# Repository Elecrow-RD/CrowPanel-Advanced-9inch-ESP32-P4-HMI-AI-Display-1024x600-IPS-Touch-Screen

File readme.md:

### 1, Product picture

### 2, Product version number

|      | Hardware | Software | Remark |
| ---- | -------- | -------- | ------ |
| 1    | V1.0     | V1.0     | old |
| 1    | V1.1     | V1.1     | old |
| 1    | V1.2     | V1.2     | latest |

**Version 1.1 Update**

The C6 module version 1.1 adds support for 4-wire SDIO communication. Additionally, the arrangement of the SDIO pins has been adjusted, with the pin mappings of the data lines D0–D3 changing from **IO14, IO15, IO16, IO17** to **IO17, IO16, IO15, IO14**. 

**Version 1.2 Update** 

Based on the V1.1 version, V1.2 further optimized the communication stability of the LoRa wireless module. At the same time, the signal pins of the wireless module socket were re-allocated: the original **IO53 and IO54** were adjusted to **IO27 and IO28** respectively, and correspondingly, **IO27 and IO28** were adjusted to **IO53 and IO54** respectively.

### 3, product information

| **Main Chip-ESP32-P4NRW32**                  |                                                              |
| -------------------------------------------- | ------------------------------------------------------------ |
| CPU/SoC                                      | **ESP32-P4**RISC-V 32-bit dual-core processor for HP systems, running at up to 400 MHz; RISC-V 32-bit single-core processor for LP systems, running at up to 40 MHz |
| System Memory                                | 768 KB L2MEM（HP）32 KB SRAM（LP）8 KB TCM 32 MB PSRAM       |
| Memory                                       | 128 KB ROM（HP）16 KB ROM（LP）16 MB Flash                   |
| Development Environment                      | ESP-IDF、Arduino IDE                                         |
| **Screen**                                   |                                                              |
| Size                                         | 9.0 inch                                                     |
| Resolution                                   | 1024*600                                                     |
| Display Panel                                | IPS Panel                                                    |
| Touch Panel                                  | Capacitive Touch, Single/5-point Touch                       |
| Viewing Angle                                | 178°                                                         |
| Brightness                                   | 400 cd/m²(Typ.)                                              |
| Color Depth                                  | 16.7M (8-bit)                                                |
| **Wireless Communication - Onboard Antenna** |                                                              |
| WiFi                                         | Support 2.4GHz(Wi-Fi6), 802.11a/b/g/n                        |
| Bluetooth                                    | Support Bluetooth 5.3 and BLE                                |
| Other                                        | Zigbee、LoRa、nRF2401、Matter、Thread and Wi-Fi Halow (Optional) |
| **Interface/Function**                       |                                                              |
| Interface                                    | USB2.0, UART, I2C, GPIO female headers, SD card holder, battery socket, speaker jack, camera header, module female headers, etc. |
| Function                                     | Audio amplifier, battery charge management, USB to UART, dual microphones, etc. |
| **Button/LED Indicator**                     |                                                              |
| Reset Button                                 | Yes, press to reset device                                   |
| Boot Button                                  | Yes, press and hold the power button to burn the program     |
| Power Button                                 | Switch On/Off                                                |
| PWR                                          | Device power on/off indication                               |
| CHG                                          | Lithium battery charging status, Low battery state           |
| **Other**                                    |                                                              |
| Installation method                          | All around mounting holes(M3 3.2mm), embedded, shell assembly |
| Operating temperature                        | -20~70 °C                                                    |
| Storage temperature                          | -30~80 °C                                                    |
| Power Input                                  | 5V/2A, USB or UART terminal                                  |
| Dimensions                                   | 222\*130*16mm                                                |

### Functional description of the product's internal interfaces:

| Pin Name | Description                                                  | Connector Type |
| :------- | :----------------------------------------------------------- | :------------- |
| SPK      | Output audio signals to connect to speakers. The main board comes with a power amplifier chip circuit. | PH2.0-2P       |
| PWR      | Power LED.                                                   |                |
| RST      | Reset button. Press it to reset the system.                  |                |
| boot     |                                                              |                |
| UART1    | Builds communication between Logic modules, including the serial communication module and the print module. | HY2.0-4P       |
| I2C      | Builds communication between Logic modules, including the serial communication module and the print module. | HY2.0-4P       |
| UART3-IN | Input power supply and serial communication functionality    | XH2.54-4P      |
| BAT      | Connect the lithium battery. (with battery charging circuit) | PH2.0-2P       |

### 4, Use the driver module

| Name | dependency library |
| ---- | ------------------ |
| LVGL | lvgl/lvgl@9.1(V1.2)<br />lvgl/lvgl@8.3(V1.0/V1.1) |

### 5,Quick Start
##### ESP-IDF starts

**Note**: This is an IDF course. Before proceeding, ensure you have Visual Studio Code and the **IDF **environment installed. The IDF version must be **5.4.2 **or higher.

1.Right-click on an empty space in the project folder and select "Open with VS Code" to open the project.

2.In the IDF plug-in, select the port, then compile and flash

### 6,Folder structure.
|--3D file： Contains 3D model files (.stp) for the hardware. These files can be used for visualization, enclosure design, or integration into CAD software.

|--Datasheet: Includes datasheets for components used in the project, providing detailed specifications, electrical characteristics, and pin configurations.

|--Eagle_SCH&PCB: Contains **Eagle CAD** schematic (`.sch`) and PCB layout (`.brd`) files. These are used for circuit design and PCB manufacturing.

|--example: Provides example code and projects to demonstrate how to use the hardware and libraries. These examples help users get started quickly.

|--factory_firmware: Stores pre-compiled factory firmware that can be directly flashed onto the device. This ensures the device runs the default functionality.

|--factory_sourcecode:  Contains the source code for the factory firmware, allowing users to modify and rebuild the firmware as needed.

|--libraries: Includes necessary libraries required for compiling and running the project. These libraries provide drivers and additional functionalities for the hardware.

### 7,Pin definition

#### ESP32-P4 9 inch and IPS Display Wiring Pins:
**DSI = Display Serial Interface**is a high-speed, low-power display interface standard defined by the MIPI Alliance, most commonly used in smartphones, tablets, Raspberry Pi devices, and embedded Linux systems.

DSI Pin connection

DSI_DATAN0--IO40

DSI_DATAN0--IO39

DSI_DATAN0--IO36

DSI_DATAN0--IO35

DSI_CLKN--IO37

DSI_CLKP--IO38

DSI_REXT--IO34

#### ESP32-P4 and Touch Driver Wiring：

i2c address: 0x5D/0x14.(The INT pin level during reset of the GT911 touch chip determines the device address.)

INT Low Level(0x5D);

INT High Level(0x14).

Pin connection

I2C1_SCL(IO46)

I2C1_SDA(IO45)

INT_TP(IO42)

RESET_TP(IO40)

#### ESP32-P4 and wireless module wiring pins：

Output voltage: 3.3V Output current: 1A max. Use: The power supply communicates with the wireless module.

Pin connection

#define RADIO_GPIO_CLK 8

#define RADIO_GPIO_MISO 7

#define RADIO_GPIO_MOSI 6

#ifdef CONFIG_BSP_SX1262_ENABLED

#define SX1262_GPIO_BUSY 9

#define SX1262_GPIO_IRQ 53

#define SX1262_GPIO_NRST 54

#define SX1262_GPIO_NSS 10

#ifdef CONFIG_BSP_NRF2401_ENABLED

#define NRF24_GPIO_IRQ 9

#define NRF24_GPIO_CE 53

#define NRF24_GPIO_CS 54

ESP32-P4 and Audio out：

Pin connection

#define AUDIO_GPIO_LRCLK    21   // GPIO pin number for LRCLK (Left-Right Clock)

#define AUDIO_GPIO_BCLK     22   // GPIO pin number for BCLK (Bit Clock)

#define AUDIO_GPIO_SDATA    23   // GPIO pin number for SDATA (Serial Data)

#define AUDIO_GPIO_CTRL     30   // GPIO pin number for audio amplifier control

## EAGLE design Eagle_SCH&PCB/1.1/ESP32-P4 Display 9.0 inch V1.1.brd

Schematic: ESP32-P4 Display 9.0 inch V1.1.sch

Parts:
0R/2A: 0R/800mA; L0805
C1, C2, C3, C10, C17, C22, C69, C86, C102, C143: 1uF; 0603
C4: 10uF/NC; 0603
C5, C7, C9, C36, C39, C40, C41, C43, C45, C46, C50, C60, C61, C63, C72, C73, C108, C113, C115, C130, C132, C145: 100nF; C0402
C6, C8, C42, C44, C47, C48, C49, C56, C71, C107, C112, C114, C116: 10uF; C0402
C11, C15, C19, C20, C21, C35, C37, C52, C53, C54, C75, C76, C77, C80, C81, C82, C84, C135, C144, C147, C150, C151, C152, C154, C155, C156, C159, C169: 100nF; 0603
C12, C27, C28, C32: 10uF/10V+; 0603
C13, C18: 22uF; C0805
C14, C16, C38, C74, C78, C79, C83, C136, C149, C153, C157: 10uF; 0603
C23, C24, C103, C104, C134, C148: 47uF; 0603
C25, C160, C161, C162, C163, C164, C165, C166, C167, C168: 10pF_NC; C0402
C26, C31: 22pF; 0603
C29, C30: 12pF; C0402
C33, C34: 15pF; C0402
C51, C55, C57, C58, C59, C64, C65, C66, C117, C118, C119, C120, C121, C122, C123, C124, C125, C126, C127, C128, C129, C131, C133, C137, C138, C139, C140, C141, C142, C146: 1uF; C0402
C62: 10nF; C0402
C67, C68, C85, C105, C106, C158: 1nF; 0603
C70: 10UF; 0603
C87: 15pF; 0603
C88: 10UF_NC; 0603
C89, C101: 22pF; C0402
C90, C99, C110: 10uF/25V; 0603
C91, C100, C111: 100nF/50V; 0603
C92: 22uF/16V; C0805
C93: 10nF/25V; 0603
C94: 10uF/25V; C0402
C95: 100nF/50V; C0402
C96, C97: 1uF/25V; 0603
C98, C109: 1uF/50V; 0603
C170, C171, C172, C173, C174, C175, C176: NC; C0402
D1: KT-0603RYG; LED_KT-0603RYG
D2, D007, D10: DSS34; D_SOD123FL
D003: NC/DSS34; D_SOD123FL
D4, D008, D11: 1N5817WS; D_SOD323
D005, D012, D013, D015, D017, D018: LMBR140ET1G
D14: Red; LED0603
D016: MM1W18_18V; LMSZ5233BT1G
D020: LMSZ5233BT1G_-6V; LMSZ5233BT1G
FB2, FB3, FB7, FB8, FB9, FB10, FB11, FB12: 1K/磁珠; L0603
FB4, FB5, FB6, FB13: 0R/800mA; L0402
FB14: 0R/800mA; R0402
FB15, FB17, FB18, FB19, FB20: 0R/2A; L0603
FB16: 0R/800mA_NC; L0603
FPC2: FPC-6PIN-0.5MM
FPC3: AFC24-S24FIA-00; FPC-SMD_P0.50-24P_QCHF-SM-H2.0
IC1: ESP32-C6-MINI-1-N4; ESP32C6MINI1N4
IC2: ME6211C18M5G-N; SOT95P282X145-5N
IC3: ME6211C28M5G-N; SOT95P282X145-5N
IC4: ME6211C18M5G-N_NC; SOT95P282X145-5N
IC5: ES7210; QFN40P400X400X80-33N
IC6: ES8311; QFN40P300X300X60-21N
IC7, IC8: ME6211C33M5G-N; SOT95P282X145-5N
IC11: W25Q128JVSIQ; SOIC127P790X216-8N
J1, J16: TYPEC-3.0-16P-SMD; USB-3.0TYPEC-SMD
J2, J13: HY2.0-4P-SMT; CONNECTOR_4P-SMD-2.0
J3, J4, J6: PH2.0WT-2PIN
J5: HOLDER-MICROSD-9P; 9P-SMD-W/-RING
J7: CONN_12X22X12_SMD; 2X12_SMD
J9, J11: HEADER-7P-18.28X2.5; H7-2.54-18.28X2.5X5MM
J10: XH2.54-4P-SMT; XH2.54-4P-SMD
J12, J14, J15, J17: THO-M3.25MM-HOLE; THO-M3.2*5MM-HOLE
J21: C23398852_30P_0.5MM_下接_FC-05A30P11H20
K3, K4: KEY-4.5X4.5; KEY-4.5X4.5-SMD
L1, L6: 2.2μH_C5179446; 1008(2520)
L2, L5: 4.7uH_C45385206_2.4A; 1008(2520)
L3: 0R; L0603
L4: NC; L0603
P1, P2, P3, P5, P6, P7, P8, P9, P10, P11, P13, P18, P19, P20, P21, P25, P26, P28, P29, P31, P32, P33, P34, P35, P36, P37, P50, P51, P52, P53, P54, P55, P57, P63, P64, P65, P66, P67, P68, P69, P70, P71, P72, P73, P74, P75, P76, P77, P78: TEST_PADPAD-1.5MM; TEST_PAD-1.5MM
Q1, Q2, Q4, Q6, Q7, Q8, Q9: BSS138W_SOT323; MOS_SOT323
Q3, Q5: XR65P02D; PDFN3333
Q10: AO3401; PMOS_SOT23
Q11: AO3401_NC; PMOS_SOT23
R1, R5, R9, R18, R53, R54, R61, R66, R67, R71, R77, R87, R91, R106, R116, R160, R180, R181: 10K; R0603@1
R2, R117, R139, R165: 100K; R0603@1
R3, R4, R17, R47, R50, R96, R101: 5.1K; R0603@1
R6, R7, R8, R10, R13, R24, R55, R60, R65, R76, R103, R112, R113, R114, R115, R118, R119, R129, R149, R184, R188, R189: 0R; R0603@1
R11: 22.1K; R0603
R12, R19, R20, R36, R37, R38, R39, R40, R41, R42, R43, R44, R70, R80, R88, R89, R90, R92, R95, R99, R100, R102, R105, R109, R124, R125, R127, R148, R162, R170, R177, R190, R200: 0R; R0402
R14, R21: NC/499K; R0603
R15, R27, R28, R29, R30, R191: 10K; 0402
R16, R31, R32, R69: 2K; R0603-SP
R22, R26, R45, R46, R51, R52, R56, R57, R58, R59, R62, R78: 4.7K; R0603@1
R23: 0R; C0402
R25: 0R; R0603-SP
R33: 10K/NC; 0402
R34, R133, R135, R136, R137, R138, R150, R151: 22R; 0402
R35: NC/10M; R0402
R48, R49, R140, R176, R183: 0R; 0402
R63, R64, R68, R108, R122, R123: 100K; R0402
R72, R73, R131, R146, R171: 10K; R0402
R74, R93, R94, R97, R98: 2K; R0603@1
R75: 2K/NC; R0603@1
R79, R147, R185: OR; R0603-SP
R81, R82, R83, R84, R85, R86: 51K; 0402
R104, R158: 4.02K; R0402
R107, R161: 0R_NC; R0402
R110, R111, R126, R128, R130: 0R/NC; R0402
R120, R121: 5.1K_NC; R0603@1
R132, R134, R141, R142, R144, R145: OR; R0402
R143: 50K; R0603-SP
R152, R153, R154, R155, R156, R157: 100R; R0402
R159: 1.4R; R0603-SP
R163: NC; R0603-SP
R164, R187: 39k; R0603@1
R166: 210K; R0603
R167: 12K; R0603
R168: 1.5K; R0402
R169: 1K; R0402
R172, R174: 3.9K; R0603
R173, R175: 51K; R0603@1
R178, R179: 20K; R0603
R182: 0R; R0805
R186: 100k; R0603@1
R210: NC/10K; R0603@1
R216, R217, R332: 22R; R0402
SW1: switch_6pin; SWITCH_6PIN_2P
TP7, TP8, TP9, TP10, TP11, TP12: TPTP08R; TP08R
U1: CH340K; ESOP-10-EP-150MIL
U2: TP4059-SOT23-6; SOT23-6L
U3, U13: NS4168; NS4168-ESOP-8
U4: NS4263B; SOP16
U6: MT9201; COOPER_SOT23-6
U7: ESP32-P4NRW32; IC_ESP32-P4NRW32
U8: UMH3NTN; SOP65P210X100-6N
U9, U10: MT3406_C22462728; SOT95P280X145-5N
U14: STC8H1K08-36I; TSSOP20
U16: MT3608; SOT95P280X145-6N
U176: LMA3526B3811; MIC-SMD_5P-L3.5-W2.7
Y2: 40MHZ; X322540MPB4SI
Y3: 24Mhz; 24MHZ_1631-24003-BTKEYA
Y4: 32.768K; NORDIC_NRF_XTAL_3215_N

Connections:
3V3$: C2.2, U1.10 (V3)
+5V_IN: D2.+, D4.+, J10.3, R46.1, R51.1
+VBUS1: D10.+, D11.+, J1.A4, J1.A9, J1.B4, J1.B9, P1.P$1
+VBUS2: D007.+, D008.+, J16.A4, J16.A9, J16.B4, J16.B9, P29.P$1
ADC_AVDD_3V3: C132.1, C133.2, FB5.2, IC5.22 (VDDA), IC5.23 (VDDM)
ADC_DVDD_3V3: C130.1, C131.2, FB4.2, IC5.6 (VDDP), IC5.7 (VDDD), R73.1
ADC_VBAT: C158.2, R164.2, R186.1, U14.13 (P3.2/ADC10)
AGND: 0R/2A.2, C102.2, C103.2, C104.2, C105.1, C106.1, C134.1, C143.1, C148.1, C154.2, FB19.2, J4.P$3, J4.P$4, R79.2, R143.1, R185.1, U4.2, U4.7, U4.15, U13.7 (GND), U13.9 (PE)
AGND1: C72.1, C117.1, C118.1, C119.1, C120.1, C121.1, C122.1, C127.2, C128.2, C129.2, C132.2, C133.1, C137.1, C138.2, C139.2, C142.2, IC5.21 (GNDA), IC6.10 (AGND), R144.1, R145.2, R171.2, R182.2, U176.5_1 (5)
AGND3: C22.2, C23.2, C24.2, C67.1, C68.1, FB20.2, J6.P$3, J6.P$4, U3.7 (GND), U3.9 (PE)
AUDIO_CTRL: Q10.3 (D), R117.2, R139.2
AUDIO_OUT_3V3: C134.2, C148.2, C154.1, FB15.2, U4.4, U4.13
AUDIO_OUT_SD: Q10.1 (G), R71.1, R147.1, U7.60 (GPIO30)
AUDIO_VDD1: C102.1, C103.1, C104.1, FB17.1, U13.6 (VDD)
AUDIO_VDD2: C22.1, C23.1, C24.1, FB18.1, U3.6 (VDD)
AUDIO_VDD_3V3: C152.2, C153.2, FB4.1, FB5.1, FB6.1, FB14.1, FB16.2, IC7.5 (VOUT)
AVDD_2V8: C82.2, C83.2, FPC3.1, FPC3.2, IC3.5 (VOUT)
C6_BOOT: IC1.23 (IO9), P36.P$1
C6_EN: C15.1, IC1.8 (EN), P37.P$1, R77.1, U7.63 (GPIO32)
C6_IO8: IC1.22 (IO8), R87.2
C6_RXD0: IC1.30 (RXD0), P21.P$1
C6_SD2_CLK: C25.2, IC1.25 (IO19), R34.2, R82.2
C6_SD2_CMD: C160.2, IC1.24 (IO18), R81.2, R133.2
C6_SD2_D0: C161.2, IC1.26 (IO20), R83.2, R135.2
C6_SD2_D1: C162.2, IC1.27 (IO21), R84.2, R136.2
C6_SD2_D2: C163.2, IC1.28 (IO22), R85.2, R137.2
C6_SD2_D3: C164.2, IC1.29 (IO23), R86.2, R138.2
C6_TXD0: IC1.31 (TXD0), P25.P$1
C6_VDD_3V3: C11.1, C14.2, IC1.3 (3V3), R76.1, R77.2, R81.1, R82.1, R83.1, R84.1, R85.1, R86.1, R87.1
CODEC_3V3: C145.1, C146.2, FB13.2, FB14.2, IC6.3 (PVDD), IC6.4 (DVDD)
CSID0_P: R153.1, U7.43 (CSI_DATAP0)
CSI_CLK_N: FPC3.19, R156.2
CSI_CLK_P: FPC3.18, R157.2
CSI_D0_N: FPC3.16, R152.2
CSI_D0_P: FPC3.15, R153.2
CSI_D1_N: FPC3.22, R154.2
CSI_D1_P: FPC3.21, R155.2
CSI_RESET: FPC3.8, Q4.2 (S), R57.2
CSI_SCL: FPC3.4, Q7.2 (S), R62.2
CSI_SDA: FPC3.5, Q6.2 (S), R56.2
DA1: J5.8 (DATA1), P74.P$1, R15.1
DA2: J5.1 (DATA2), P72.P$1, R30.1
DOVDD_1V8: C77.2, C78.2, C84.2, C85.2, FPC3.9, IC2.5 (VOUT), Q4.1 (G), Q6.1 (G), Q7.1 (G), R56.1, R57.1, R62.1, R67.2, Y3.4 (4_VDD)
DOWNLOAD_BOOT: R60.1, R106.2
DSI_CLK_N: J21.18, R100.1, TP11.TP
DSI_CLK_P: J21.17, R102.1, TP12.TP
DSI_DATA0_N: J21.24, R190.1, TP7.TP
DSI_DATA0_P: J21.23, R92.1, TP8.TP
DSI_DATA1_N: J21.21, R95.1, TP9.TP
DSI_DATA1_P: J21.20, R99.1, TP10.TP
DTR: R5.2, U1.4 (DTR#), U8.4 (E2)
EN_DCDC: R13.2, U7.79 (EN_DCDC)
ESP32_LDO1: C58.1, R105.2, U7.71 (VFB1/VO1)
ESP32_LDO2: C57.1, R40.2, U7.72 (VFB2/VO2)
ESP32_LDO3: C59.1, R80.2, U7.73 (VFB3/VO3)
ESP32_LDO4: C66.1, R109.2, U7.74 (VFB4/VO4)
FB_DCDC: C31.1, R14.2, R21.1, R103.1, U10.5 (FB)
FLASH_CK: IC11.6 (CLK), U7.32 (FLASH_CK)
FLASH_CS: IC11.1 (/CS), R146.1, U7.27 (FLASH_CS)
FLASH_D: IC11.5 (DI_(IO0)), U7.33 (FLASH_D)
FLASH_HOLD: IC11.7 (/HOLD_OR_/RESET_(IO3)), U7.31 (FLASH_HOLD)
FLASH_Q: IC11.2 (DO_(IO1)), U7.28 (FLASH_Q)
FLASH_WP: IC11.3 (/WP_(IO2)), U7.29 (FLASH_WP)
GND: 0R/2A.1, C1.1, C2.1, C3.1, C4.1, C5.2, C6.1, C7.2, C8.1, C9.2, C10.1, C11.2, C12.2, C13.2, C14.1, C15.2, C16.1, C17.1, C18.2, C19.2, C20.1, C21.1, C25.1, C27.1, C28.2, C29.2, C30.2, C32.1, C33.2, C34.1, C35.1, C36.2, C37.1, C38.1, C39.2, C40.2, C41.2, C42.1, C43.2, C44.1, C45.2, C46.2, C47.1, C48.1, C49.1, C50.2, C51.2, C52.1, C53.1, C54.1, C55.2, C56.1, C57.2, C58.2, C59.2, C60.2, C61.2, C62.2, C63.2, C64.2, C65.2, C66.2, C69.1, C70.2, C71.1, C73.2, C74.1, C75.1, C76.1, C77.1, C78.1, C79.1, C80.1, C81.1, C82.1, C83.1, C84.1, C85.1, C86.1, C87.1, C88.2, C90.2, C91.2, C92.2, C94.2, C95.2, C98.2, C99.2, C100.2, C107.1, C108.2, C109.2, C110.2, C111.2, C112.1, C113.2, C114.1, C115.2, C116.1, C130.2, C131.1, C136.1, C144.1, C145.2, C146.1, C149.1, C150.1, C151.1, C152.1, C153.1, C155.1, C156.1, C157.1, C158.1, C159.1, C160.1, C161.1, C162.1, C163.1, C164.1, C165.1, C166.1, C167.1, C168.1, C169.2, C170.1, C171.1, C172.1, C173.1, C174.1, C175.1, C176.1, D14.-, D016.2, D018.1, D020.1, FB19.1, FB20.1, FPC2.4, FPC2.7, FPC2.8, FPC3.3, FPC3.6, FPC3.10, FPC3.12, FPC3.17, FPC3.20, FPC3.25, FPC3.26, IC1.1 (GND_1), IC1.2 (GND_2), IC1.11 (GND_3), IC1.14 (GND_4), IC1.36 (GND_5), IC1.37 (GND_6), IC1.38 (GND_7), IC1.39 (GND_8), IC1.40 (GND_9), IC1.41 (GND_10), IC1.42 (GND_11), IC1.43 (GND_12), IC1.44 (GND_13), IC1.45 (GND_14), IC1.46 (GND_15), IC1.47 (GND_16), IC1.48 (GND_17), IC1.49 (GND_18), IC1.50 (GND_19), IC1.51 (GND_20), IC1.52 (GND_21), IC1.53 (GND_22), IC1.54 (GND_23), IC1.55 (GND_24), IC1.56 (GND_25), IC1.57 (GND_26), IC1.58 (GND_27), IC1.59 (GND_28), IC1.60 (GND_29), IC1.61 (GND_30), IC2.2 (VSS), IC3.2 (VSS), IC4.2 (VSS), IC5.8 (GNDD), IC5.33 (EP), IC6.5 (DGND), IC6.20 (CE), IC6.21 (EP), IC7.2 (VSS), IC8.2 (VSS), IC11.4 (GND), J1.A1, J1.A12, J1.B1, J1.B12, J1.P$1, J1.P$2, J1.P$3, J1.P$4, J2.4, J2.SS1, J2.SS2, J3.P$2, J3.P$3, J3.P$4, J5.6 (VSS), J5.G1, J5.G2, J5.G3, J5.G4, J7.7, J7.8, J7.10, J7.21, J7.22, J7.23, J7.24, J9.6, J9.6-6 (6), J10.4, J10.5 (SS1), J10.6 (SS2), J12.P$1, J13.4, J13.SS1, J13.SS2, J14.P$1, J15.P$1, J16.A1, J16.A12, J16.B1, J16.B12, J16.P$1, J16.P$2, J16.P$3, J16.P$4, J17.P$1, J21.10, J21.13, J21.16, J21.19, J21.22, J21.25, J21.31, J21.32, K3.1, K4.1, P10.P$1, P28.P$1, P31.P$1, P57.P$1, P65.P$1, P66.P$1, P67.P$1, P68.P$1, P69.P$1, P70.P$1, P78.P$1, R3.1, R4.2, R11.2, R16.1, R18.1, R21.2, R33.2, R64.1, R72.1, R96.1, R101.2, R104.1, R108.1, R123.1, R158.2, R159.1, R160.2, R163.1, R167.1, R169.1, R173.1, R175.1, R182.1, R186.2, SW1.1 (1_2B), SW1.6 (6_1B), U1.3 (GND), U1.EP, U2.2 (GND), U6.2 (2-GND), U7.105 (GND), U9.2 (GND), U10.2 (GND), U14.10 (GND), U16.2 (2_GND), Y2.2 (GND_1), Y2.4 (GND_2), Y3.2 (2_GND)
I2C1_SCL: FPC2.1, Q9.2 (S), R97.2, U7.88 (GPIO46)
I2C1_SCL_3V3: IC6.1 (CCLK), J11.2, J11.2-2 (2), J13.1, Q9.3 (D), R93.2, R125.1, R189.2
I2C1_SDA: FPC2.2, Q8.2 (S), R98.2, U7.87 (GPIO45)
I2C1_SDA_3V3: IC6.19 (CDATA), J11.3, J11.3-3 (3), J13.2, Q8.3 (D), R94.2, R124.1, R188.2
I2C2_SCL: Q7.3 (D), R59.2, R89.2
I2C2_SDA: Q6.3 (D), R22.2, R90.2
I2SOUT_LRCK1: R149.2, U13.2 (LRCLK)
I2SOUT_LRCK2: P35.P$1, R114.2, U3.2 (LRCLK)
I2SOUT_SCLK1: R129.2, U13.3 (BCLK)
I2SOUT_SCLK2: P34.P$1, R113.2, U3.3 (BCLK)
I2SOUT_SD1: R112.2, U13.4 (SDATA)
I2SOUT_SD2: P33.P$1, R115.2, U3.4 (SDATA)
I2S_LRCK: R114.1, R130.1, R149.1, U7.23 (GPIO21)
I2S_LRCK_N: IC5.10 (LRCK), IC6.8 (LRCK), R130.2
I2S_MCLK: R126.1, R127.1, U7.52 (GPIO24)
I2S_MCLK_N: IC5.5 (MCLK), IC6.2 (MCLK), R126.2
I2S_SCLK: R113.1, R128.1, R129.1, U7.24 (GPIO22)
I2S_SCLK_N: IC5.9 (SCLK), IC6.6 (SCLK/DMIC_SCL), R128.2
I2S_SDIN1_N: IC5.11 (SDOUT1/TDMOUT)
I2S_SDIN2: R161.1, R162.1, U7.55 (GPIO26)
I2S_SDIN2_N: IC5.12 (SDOUT2/TDMIN), R161.2
I2S_SDOUT: R111.1, R112.1, R115.1, U7.25 (GPIO23)
I2S_SDOUT_N: IC6.9 (DSDIN), R111.2
INLN: C147.1, R148.2
INLN1: R179.1, U4.6
INRN: C135.1, R200.2
INRN1: R178.1, U4.11
INT_TP: FPC2.3, R75.2, U7.83 (GPIO42)
IO1: R89.1, U7.14 (GPIO13)
IO8: R217.1, U7.8 (GPIO8)
IO9_W: C175.2, J11.5, J11.5-5 (5), R150.2
IO10_W_BUSY: C174.2, J11.6, J11.6-6 (6), R151.2
IO46_CSI_RESET: Q4.3 (D), R58.2, R88.2
LCD_AVDD_9V6: C92.1, C93.1, D005.2, D013.1, J21.9, P19.P$1, R166.2, R168.2
LCD_BK_EN: R160.1, U6.4 (4-EN), U7.61 (GPIO31)
LCD_BK_POWER: Q11.1 (G), R180.1, U7.58 (GPIO29)
LCD_BK_VDD: C13.1, C17.2, L5.1, Q11.3 (D), R184.2, U6.6 (6-VIN)
LCD_RESET: J21.27, P50.P$1, R69.2, U7.82 (GPIO41)
LCD_VCOM_3V3: C94.1, C95.1, J21.30, P20.P$1, R168.1, R169.2
LCD_VDD: C37.2, C38.2, C52.2, C53.2, FPC2.5, IC4.5 (VOUT), J21.28, J21.29, R63.2, R65.1, R68.2, R122.2
LCD_VGH_18V: C99.1, C100.1, D016.1, J21.3, P18.P$1, R172.1, R173.2
LCD_VGL_-6V: C110.1, C111.1, D020.2, J21.4, P71.P$1, R174.1, R175.2
LED+: C18.1, C19.1, D003.-, D012.1, P63.P$1, R25.1, U6.5 (5-OV)
LED-: J21.7, J21.8, P64.P$1, R159.2, R163.2, U6.3 (3-FB)
MIC1N: C89.2
MIC1P: C101.2
MIC2N: C125.2, R141.2
MIC2P: C126.2, R142.2
MIC2_1: R132.2, R142.1, U176.1
MIC2_2: R131.1, R141.1, R145.1, R171.1, U176.2
MIC2_3: R134.1, R144.2, U176.3
MIC2_VDD_3V3: C72.2, FB6.2, U176.4
MIC3N: C124.1, R170.2
MIC3P: C123.1, R177.2
MIC_L/R: R131.2, U7.22 (GPIO20)
MIC_MCLK: R127.2, R134.2
MIC_SD2: R132.1, R162.2
unnamed: R1.1, U9.1 (EN)
unnamed: L1.1, U9.3 (SW)
unnamed: FB7.1, U4.12
unnamed: FB10.1, U13.8 (VOP)
unnamed: R6.1, U1.1 (UD+)
unnamed: R7.1, U1.2 (UD-)
unnamed: R5.1, U8.2 (B1)
unnamed: R9.1, U8.5 (B2)
unnamed: J1.B5, R3.2
unnamed: R8.2, U1.9 (RXD)
unnamed: R10.2, U1.8 (TXD)
unnamed: R16.2, U2.6 (PRO)
unnamed: C26.1, R2.2, R11.1, U9.5 (FB)
unnamed: L6.1, U10.3 (SW)
unnamed: C151.2, IC7.3 (CE), R181.1
unnamed: R13.1, R210.2, U10.1 (EN)
unnamed: C143.2, U4.10
unnamed: R185.2, U4.8
unnamed: D1.3, R31.1, R121.1
unnamed: D1.4, R32.1, R120.1
unnamed: D14.+, R26.1
unnamed: J21.1, J21.2, R25.2
unnamed: C173.2, J9.1, J9.1-1 (1), R49.1
unnamed: C176.2, J11.1, J11.1-1 (1), R48.1
unnamed: FB8.1, U4.14
unnamed: Q5.4 (4_G), R78.1, SW1.2 (2_COM2), SW1.5 (5_COM1)
unnamed: J1.A5, R4.1
unnamed: R79.1, U4.16
unnamed: C28.1, R24.1, R210.1, U10.4 (VIN)
unnamed: R90.1, U7.13 (GPIO12)
unnamed: R88.1, U7.12 (GPIO11)
unnamed: R190.2, U7.40 (DSI_DATAN0)
unnamed: R92.2, U7.39 (DSI_DATAP0)
unnamed: C30.1, R35.1, U7.1 (GPIO1), Y4.2
unnamed: C29.1, R35.2, U7.104 (GPIO0), Y4.1
unnamed: R95.2, U7.36 (DSI_DATAN1)
unnamed: R99.2, U7.35 (DSI_DATAP1)
unnamed: R100.2, U7.37 (DSI_CLKN)
unnamed: C147.2, R179.2
unnamed: R102.2, U7.38 (DSI_CLKP)
unnamed: R103.2, U7.78 (FB_DCDC)
unnamed: R104.2, U7.34 (DSI_REXT)
unnamed: C21.2, IC4.3 (CE), R53.1
unnamed: C135.2, R178.2
unnamed: FB2.1, U3.8 (VOP)
unnamed: FB11.1, U13.5 (VON)
unnamed: FB3.1, U3.5 (VON)
unnamed: R117.1, U3.1 (CTRL)
unnamed: R118.2, U14.12 (P3.1/ADC9)
unnamed: R119.2, U14.11 (P3.0/ADC8)
unnamed: R139.1, R143.2, U13.1 (CTRL)
unnamed: IC5.3 (CDATA), R124.2
unnamed: IC5.4 (CCLK), R125.2
unnamed: FB9.1, U4.3
unnamed: C155.2, IC8.3 (CE), R116.1
unnamed: C159.2, R187.2, U14.7 (NRST/PWM6/P5.4)
unnamed: R188.1, U14.3 (MISO/P1.4)
unnamed: FB12.1, U4.5
unnamed: C124.2, IC5.32 (MIC3N)
unnamed: C89.1, IC5.15 (MIC1N)
unnamed: C101.1, IC5.16 (MIC1P)
unnamed: R189.1, U14.4 (SCLK/P1.5)
unnamed: R332.1, U7.7 (GPIO7)
unnamed: R216.1, U7.6 (GPIO6)
unnamed: R150.1, U7.10 (GPIO9)
unnamed: R151.1, U7.11 (GPIO10)
unnamed: R158.1, U7.48 (CSI_REXT)
unnamed: R157.1, U7.44 (CSI_CLKP)
unnamed: R156.1, U7.45 (CSI_CLKN)
unnamed: R155.1, U7.47 (CSI_DATAP1)
unnamed: R154.1, U7.46 (CSI_DATAN1)
unnamed: R152.1, U7.42 (CSI_DATAN0)
unnamed: J16.B5, R96.2
unnamed: J16.A5, R101.1
unnamed: C123.2, IC5.31 (MIC3P)
unnamed: C122.2, IC5.30 (REFQ34)
unnamed: C121.2, IC5.29 (REFP34)
unnamed: C76.2, IC2.3 (CE), R61.1
unnamed: C81.2, IC3.3 (CE), R66.1
unnamed: C86.2, R67.1, Y3.1 (1_EN)
unnamed: C120.2, IC5.28 (MIC4P)
unnamed: C119.2, IC5.27 (MIC4N)
unnamed: C118.2, IC5.26 (MICBIAS34)
unnamed: C117.2, IC5.25 (REFQM)
unnamed: C129.1, IC5.24 (MICBIAS12)
unnamed: C125.1, IC5.20 (MIC2N)
unnamed: C126.1, IC5.19 (MIC2P)
unnamed: C127.1, IC5.18 (REFQ12)
unnamed: C128.1, IC5.17 (REFP12)
unnamed: R147.2, U4.1
unnamed: C97.2, D017.1, D018.2
unnamed: IC5.1 (AD0), R73.2
unnamed: IC5.2 (AD1), R72.2
unnamed: C139.1, IC6.14 (DACVREF)
unnamed: C137.2, IC6.16 (VMID)
unnamed: C138.1, IC6.15 (ADCVREF)
unnamed: C140.1, IC6.13 (OUTN)
unnamed: C141.1, IC6.12 (OUTP)
unnamed: C142.1, FB13.1, IC6.11 (AVDD)
unnamed: D003.+, D012.2, L5.2, U6.1 (1-SW)
unnamed: C96.1, C97.1, D013.2, L2.2, U16.1 (1_SW)
unnamed: R165.2, U16.4 (4_EN)
unnamed: C96.2, D005.1, D015.2
unnamed: C93.2, R166.1, R167.2, U16.3 (3_FB)
unnamed: C98.1, D015.1, R172.2
unnamed: C140.2, R170.1, R200.1
unnamed: C109.1, D017.2, R174.2
unnamed: C141.2, R148.1, R177.1
P4_IO2: J7.9, U7.2 (GPIO2)
P4_IO3: J7.11, U7.3 (GPIO3)
P4_IO4: J7.13, U7.4 (GPIO4)
P4_IO5: J7.15, U7.5 (GPIO5)
P4_IO25: J7.17, U7.53 (GPIO25)
P4_IO27: J7.19, U7.56 (GPIO27)
P4_IO28: J7.20, U7.57 (GPIO28)
P4_IO35: R55.2, U7.66 (GPIO35)
P4_IO36: R60.2, U7.68 (GPIO36)
P4_IO49: J7.18, U7.92 (GPIO49)
P4_IO50: J7.16, U7.93 (GPIO50)
P4_IO51: J7.14, U7.94 (GPIO51)
P4_IO52: J7.12, U7.95 (GPIO52)
P4_RST_EN: C35.2, K4.2, R54.2, U7.103 (CHIP_PU), U8.6 (C1)
P4_RXD2: R48.2, U7.98 (GPIO54)
P4_TXD2: R49.2, U7.97 (GPIO53)
P4_VBAT: C9.1, C42.2, R20.1, U7.102 (VBAT)
POWER_CHRG: R50.1, R120.2, U2.1 (CHG), U14.14 (P3.3/ADC11)
POWER_DONE: R47.1, R121.2, U2.5 (STD), U14.15 (P3.4/ADC11)
POWER_G_LED: R31.2, U14.17 (P3.6/ADC14)
POWER_R_LED: R32.2, U14.16 (P3.5/ADC13)
RESET_TP: FPC2.6, R74.2, U7.81 (GPIO40)
RTS: R9.2, U1.6 (RTS#), U8.1 (E1)
RXD0: R10.1, U7.70 (GPIO38)
RXD1: J2.1, U7.90 (GPIO48)
RXD3: Q2.2 (S), R45.2, U7.64 (GPIO33)
SD1_CMD: C166.2, J5.3 (DI), P8.P$1, R28.1, R140.1
SD1_CMD4: R140.2, U7.86 (GPIO44)
SD1_D0: C168.2, J5.7 (DO), P6.P$1, R27.1, R183.1
SD1_D04: R183.2, U7.80 (GPIO39)
SD1_SCK: C167.2, J5.5 (SCLK), P7.P$1, R176.1, R191.1
SD1_SCK4: R176.2, U7.84 (GPIO43)
SD2_CLK: R34.1, U7.19 (GPIO18)
SD2_CMD: R133.1, U7.20 (GPIO19)
SD2_D0: R135.1, U7.18 (GPIO17)
SD2_D1: R136.1, U7.17 (GPIO16)
SD2_D2: R137.1, U7.16 (GPIO15)
SD2_D3: R138.1, U7.15 (GPIO14)
SDCS: C165.2, J5.2 (CS), P73.P$1, R29.1, R33.1
SHLR: J21.6, P52.P$1, R122.1, R123.2
SPI2_MISO: C171.2, J9.3, J9.3-3 (3), R332.2
SPI2_MOSI: C170.2, J9.4, J9.4-4 (4), R216.2
SPI2_SCK: C172.2, J9.2, J9.2-2 (2), R217.2
SPI_BOOT: C54.2, K3.2, R55.1, R91.2, U8.3 (C2)
STBYB: J21.26, P51.P$1, R63.1, R64.2
STC8_RXD: P76.P$1, R119.1
STC8_TXD: P75.P$1, R118.1
STC8_VDD_3V3: C69.2, C156.2, C157.2, IC8.5 (VOUT), P77.P$1, R187.1, U14.8 (VCC), U14.9 (VREF)
TXD0: R8.1, U7.69 (GPIO37)
TXD1: J2.2, U7.89 (GPIO47)
TXD3: Q1.2 (S), R52.2, U7.65 (GPIO34)
UART_IN_RXD3: J10.2, Q2.3 (D), R46.2
UART_IN_TXD3: J10.1, Q1.3 (D), R51.2
UPDN: J21.5, P53.P$1, R68.1, R108.2
USB1_D+: J1.A6, J1.B6, P2.P$1, R6.2
USB1_D-: J1.A7, J1.B7, P3.P$1, R7.2
USB2_D+: J16.A6, J16.B6, U7.50 (DP)
USB2_D-: J16.A7, J16.B7, U7.49 (DM)
VBAT: C4.2, J3.P$1, P9.P$1, Q3.5 (5_D), Q3.6 (6_D), Q3.7 (7_D), Q3.8 (8_D), Q3.9 (9_D), R17.1, R164.1, U2.3 (BAT)
VCC5V: C136.2, C144.2, D1.1, D1.2, D2.-, D007.-, D10.-, IC8.1 (VIN), P11.P$1, Q3.1 (1_S), Q3.2 (2_S), Q3.3 (3_S), Q5.1 (1_S), Q5.2 (2_S), Q5.3 (3_S), R78.2, R116.2
VCC5V_IN: C3.2, D4.-, D008.-, D11.-, Q3.4 (4_G), R17.2, R18.2, R47.2, R50.2, U2.4 (VCC)
VCCA: C43.1, C47.2, R23.1, U7.51 (VCCA)
VDD5V: C12.1, C74.2, C75.2, C79.2, C80.2, C90.1, C91.1, C149.2, C150.2, FB15.1, FB17.2, FB18.2, IC2.1 (VIN), IC3.1 (VIN), IC7.1 (VIN), J7.2, J7.4, J7.6, L2.1, L4.2, P5.P$1, Q5.5 (5_D), Q5.6 (6_D), Q5.7 (7_D), Q5.8 (8_D), Q5.9 (9_D), Q11.2 (S), R1.2, R24.2, R26.2, R61.2, R66.2, R165.1, R180.2, R181.2, R184.1, U9.4 (VIN), U16.5 (5_IN)
VDD5V_W: C88.1, J9.7, J9.7-7 (7), L4.1
VDDA: C7.1, C8.2, R19.1, U7.101 (VDDA)
VDDPST: C36.1, C55.1, R40.1, R110.1, U7.59 (VDDPST), U7.67 (VDDPST)
VDDPST_1: C73.1, C107.2, R36.1, U7.9 (VDDPST_1)
VDDPST_2: C41.1, C44.2, R37.1, U7.21 (VDDPST_2)
VDDPST_3: C45.1, C49.2, R38.1, U7.30 (VDDPST_3)
VDDPST_4: C50.1, C56.2, R39.1, U7.62 (VDDPST_4)
VDDPST_5: C60.1, C65.1, Q8.1 (G), Q9.1 (G), R69.1, R74.1, R75.1, R97.1, R98.1, R109.1, U7.85 (VDDPST_5)
VDDPST_6: C61.1, C71.2, R41.1, U7.96 (VDDPST_6)
VDDPST_DCDC: C5.1, C6.2, R12.1, U7.77 (VDDPST_DCDC)
VDDPST_LDO: C46.1, C48.2, R70.1, U7.75 (VDDPST_LDO)
VDD_1V2: C31.2, C32.2, L6.2, R14.1, R42.2, R43.2, R44.2
VDD_3V3: C1.2, C10.2, C16.2, C20.2, C26.2, C27.2, FB16.1, IC4.1 (VIN), J2.3, J5.4 (VDD), J7.1, J7.3, J7.5, J13.3, L1.2, L3.2, P13.P$1, Q1.1 (G), Q2.1 (G), Q10.2 (S), R2.1, R12.2, R15.2, R19.2, R20.2, R22.1, R23.2, R27.2, R28.2, R29.2, R30.2, R36.2, R37.2, R38.2, R39.2, R41.2, R45.1, R52.1, R53.2, R54.1, R58.1, R59.1, R65.2, R70.2, R71.2, R76.2, R91.1, R93.1, R94.1, R106.1, R107.2, R110.2, R191.2, U1.7 (VCC)
VDD_3V3_A: C70.1, C169.1, J9.5, J9.5-5 (5), L3.1
VDD_FLASH: C39.1, C40.1, C51.1, IC11.8 (VCC), R105.1, R107.1, R146.2
VDD_HP_0: C108.1, C112.2, R42.1, U7.26 (VDD_HP_0)
VDD_HP_2: C113.1, C114.2, R43.1, U7.76 (VDD_HP_2)
VDD_HP_3: C115.1, C116.2, R44.1, U7.91 (VDD_HP_3)
VDD_MIPI_DPHY: C62.1, C63.1, C64.1, R80.1, U7.41 (VDD_MIPI_DPHY)
VOLN: C106.2, FB11.2, FB12.2, J4.P$2, P55.P$1
VOLP: C105.2, FB9.2, FB10.2, J4.P$1, P54.P$1
VORN: C68.2, FB3.2, FB7.2, J6.P$2, P32.P$1
VORP: C67.2, FB2.2, FB8.2, J6.P$1, P26.P$1
XTAL_N: C34.2, U7.99 (XTAL_N), Y2.3 (CRYSTAL_2)
XTAL_P: C33.1, U7.100 (XTAL_P), Y2.1 (CRYSTAL_1)
XVCLK: C87.2, FPC3.11, Y3.3 (3_OUT)

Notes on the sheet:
BOOT
RESET
HIG: SPI Boot
LOW: Download Boot
HIG: ESP32-P4 Enable
LOW: ESP32-P4 Off
Power_LED
USB interface
USB TO UART
Battery and control
ESP32-C6
9.0 inch IPS interface
SD card
Wireless module
UART & I2C & GPIO extensions
PDM MIC
UART_5V_IN
I2C_OUT
UART0_OUT
ESP32-P4
ESP32-P4_POWER
CSI_Interface
I led=200mV/1.4=142mA
DSI_LED Driver
Audio_OUT
DC-DC:5V to 3V3
DC-DC:5V to 1V2
Power SW
LCD_POWER
Audio_ADC/DAC
LDO:5V to 3V3(AUDIO POWER)
ESP32 P4-Advance HMI Display 9.0 V1.0
Charge indicator control

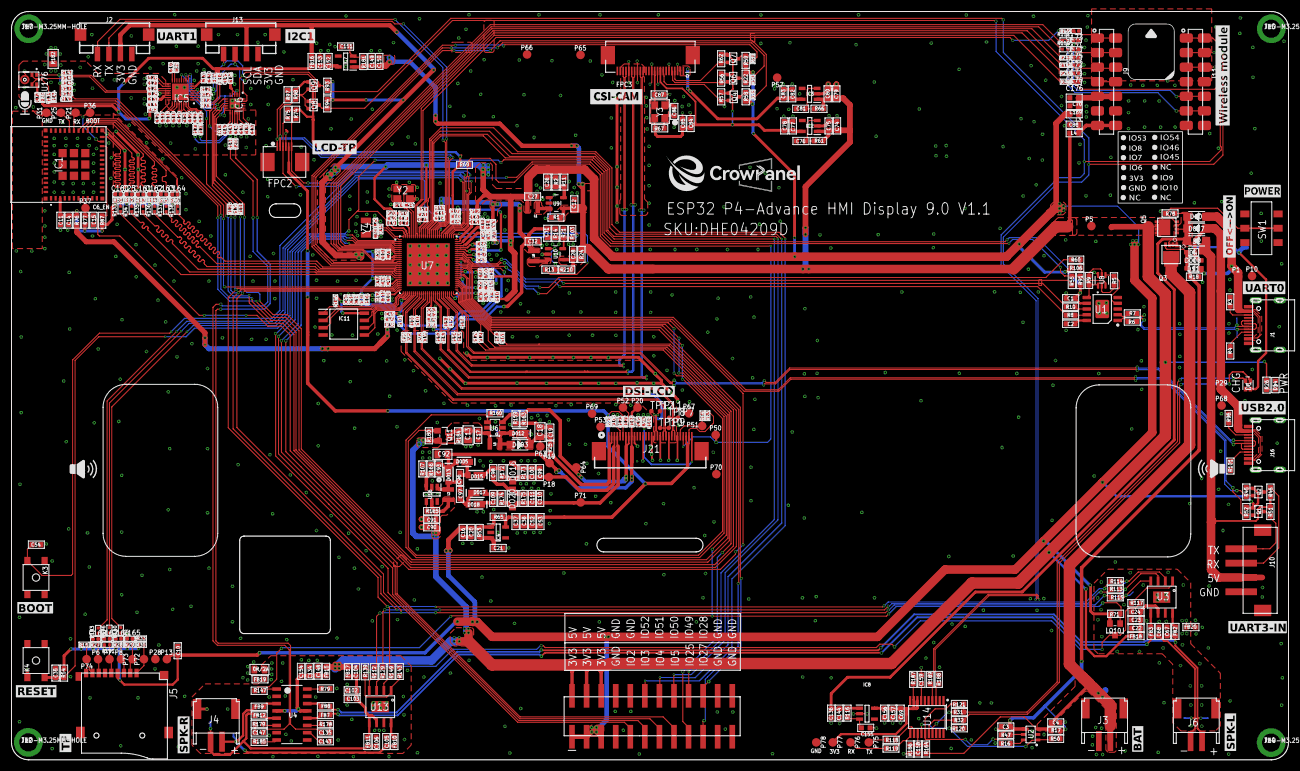
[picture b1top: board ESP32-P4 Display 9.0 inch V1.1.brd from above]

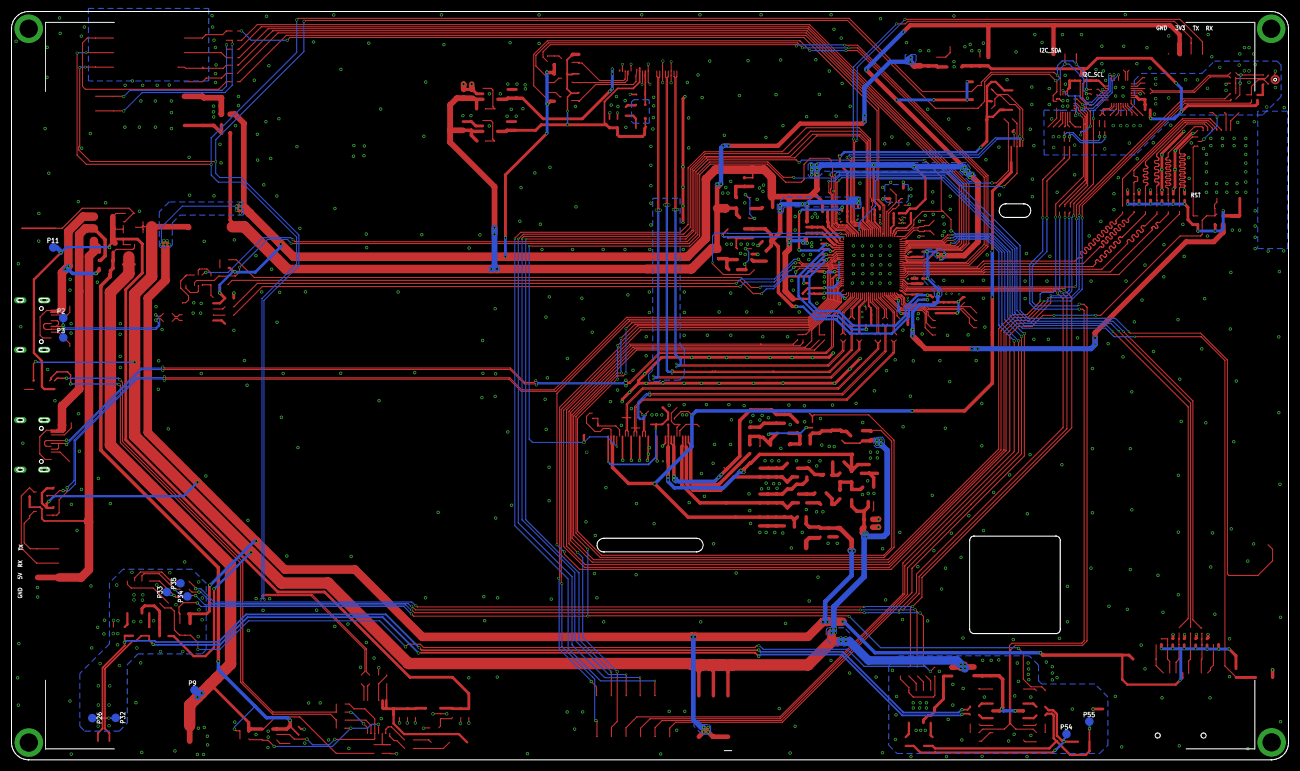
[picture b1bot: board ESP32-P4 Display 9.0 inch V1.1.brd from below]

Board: 2 copper layers, 222.7 x 130.5 mm, 528 parts (11 on the bottom side), 315 nets.

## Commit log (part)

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2026-01-02 add new files
2026-01-09 refactor: move xxx file to new path
2026-03-18 add arduino
2026-03-18 Update LVGL dependency version in README
2026-05-12 sync idf lesson13
2026-06-04 sync example/V1.1 V1.2

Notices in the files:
parts and their libraries:
SparkFun-Coils: Licensing: Creative Commons ShareAlike 4.0 International - https://creativecommons.org/licenses/by-sa/4.0
